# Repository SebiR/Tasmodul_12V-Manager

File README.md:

# 12V Power Management
A Tasmota compatible power selector for Caravans including automatic power source switching between on-board battery, car power and a mains PSU.
A INA226 measures the output voltage and current, the presence of the power sources are also available on GPIOs.

## Features
* Up to 15A (10A nom.)
* Fused inputs
* Current and voltage measurement
* Automatic source switching with priorities (hard-wired)

## Tasmota Configuration
Tasmota won't probe the INA226 unless full-scale current and the value of the shunt resistor are set.
 
`Sensor54 10 Return channel 1 shunt resistance and full scale current`

`Sensor54 11 [shunt_resistance] Set INA226 channel 1 shunt resistance in ohms, floating point`

`Sensor54 12 [full_scale_current] Set INA226 channel 1 full scale current in amperes, floating point`

So with the `Sensor54` command, we can set the current and the resistance for our board:

`Sensor54 11 0.002`

`Sensor54 12 15`

After that, we can see the current and the voltage in Tasmota.

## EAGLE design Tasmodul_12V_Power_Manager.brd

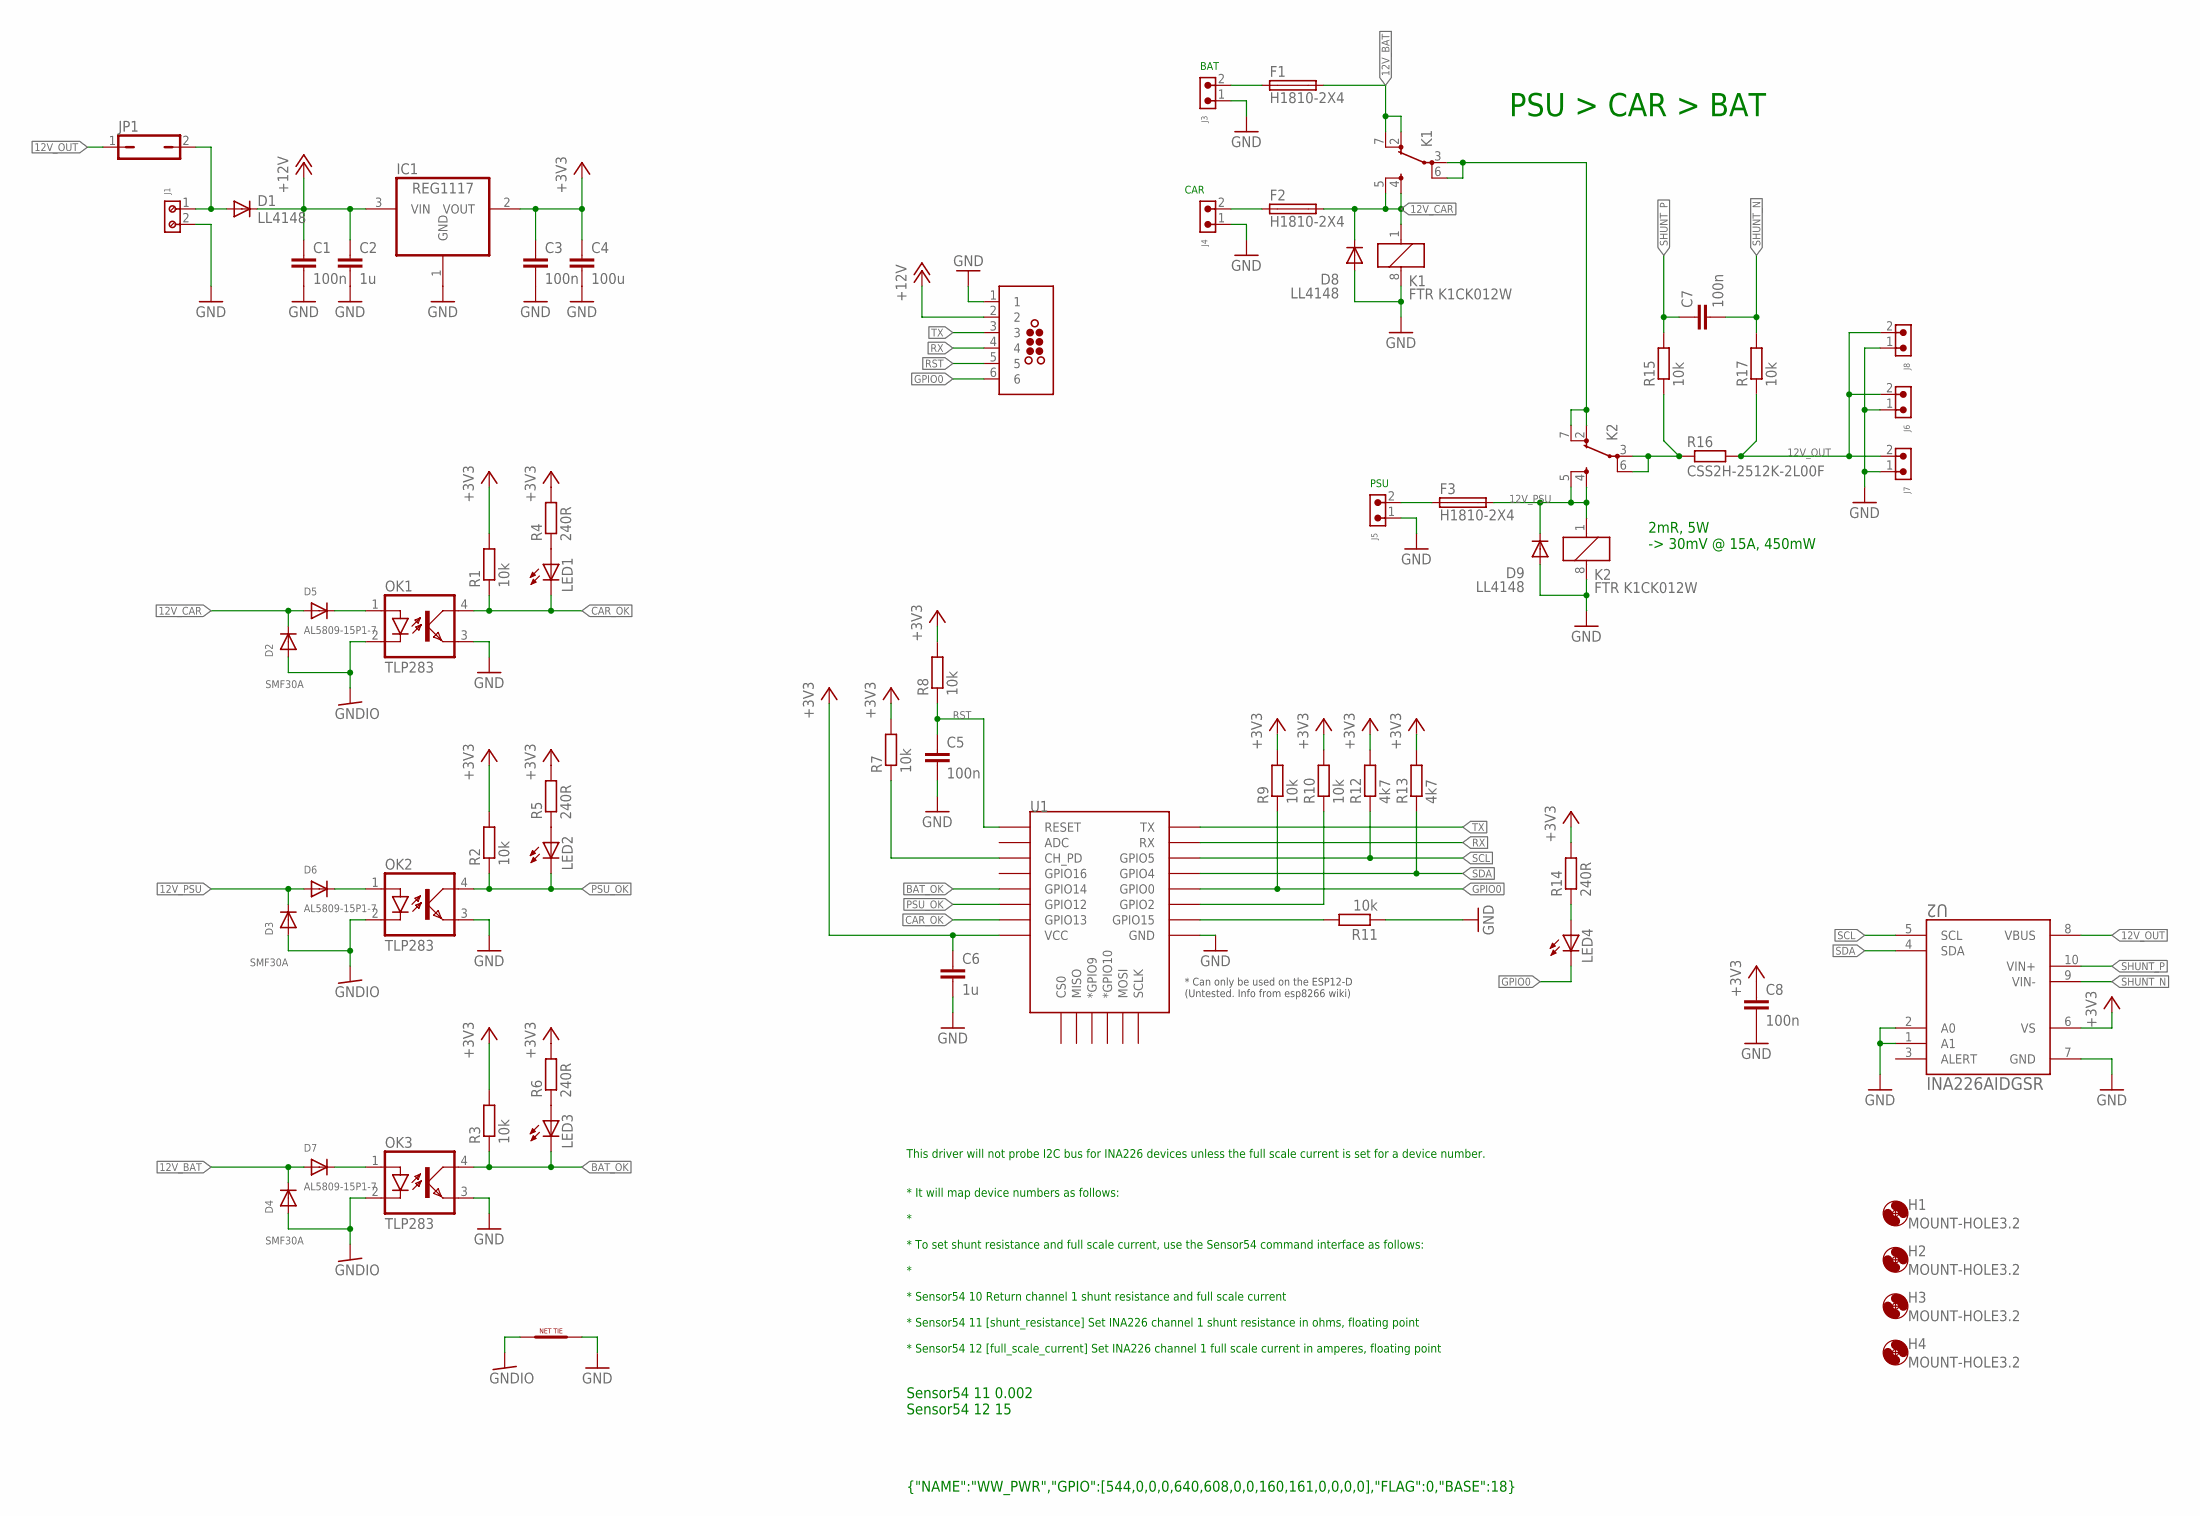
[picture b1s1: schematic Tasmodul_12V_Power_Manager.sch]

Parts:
C1, C3, C5, C7, C8: 100n; C0603
C2, C6: 1u; C0603
C4: 100u; C0603
D1, D8, D9: LL4148; MINIMELF
D2, D3, D4: SMF30A; SOD-123FL
D5, D6, D7: AL5809-15P1-7; SOD-123FL
F1, F2, F3: H1810-2X4
H1, H2, H3, H4: MOUNT-HOLE3.2; 3,2
IC1: REG1117; SOT223
J1: 691210910002
J2: TC2030-MCP-NL
J3, J4, J5, J6, J7, J8: 691313510002
JP1: JP1Q; JP1
K1, K2: FTR K1CK012W; FTR-K1C
LED1, LED2, LED3, LED4: LEDCHIP-LED0603; CHIP-LED0603
NT1: NET_TIE0.5MM; NET_TIE_0.5
OK1, OK2, OK3: TLP283; MINI-FLAT-4
R1, R2, R3, R7, R8, R9, R10, R11, R15, R17: 10k; R0603
R4, R5, R6, R14: 240R; R0603
R12, R13: 4k7; R0603
R16: CSS2H-2512K-2L00F
U1: ESP12ESMD; ESP12E-SMD
U2: INA226AIDGSR; DGS10

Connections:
12V_BAT: D4.C, D7.A, F1.B1 (2), F1.B2 (2), F1.B3 (2), F1.B4 (2), K1.2 (OA), K1.7 (OB)
12V_CAR: D2.C, D5.A, D8.C, F2.B1 (2), F2.B2 (2), F2.B3 (2), F2.B4 (2), K1.1, K1.4 (SA), K1.5 (SB)
12V_OUT: J6.2, J7.2, J8.2, JP1.1, R16.2, R17.1, U2.8 (VBUS)
12V_PSU: D3.C, D6.A, D9.C, F3.B1 (2), F3.B2 (2), F3.B3 (2), F3.B4 (2), K2.1, K2.4 (SA), K2.5 (SB)
+3V3: C3.1, C4.1, C6.1, C8.1, IC1.2 (VOUT), R1.2, R2.2, R3.2, R4.2, R5.2, R6.2, R7.2, R8.2, R9.2, R10.2, R12.2, R13.2, R14.2, U1.VCC, U2.6 (VS)
+12V: C1.1, C2.1, D1.C, IC1.3 (VIN), J2.2
BAT_OK: LED3.C, OK3.4 (COL), R3.1, U1.GPIO14
CAR_OK: LED1.C, OK1.4 (COL), R1.1, U1.GPIO13
GND: C1.2, C2.2, C3.2, C4.2, C5.2, C6.2, C8.2, D8.A, D9.A, IC1.1 (GND), J1.2, J2.1, J3.1, J4.1, J5.1, J6.1, J7.1, J8.1, K1.8 (2), K2.8 (2), NT1.NET2, OK1.3 (EMIT), OK2.3 (EMIT), OK3.3 (EMIT), R11.1, U1.GND, U2.1 (A1), U2.2 (A0), U2.7 (GND)
GNDIO: D2.A, D3.A, D4.A, NT1.NET1, OK1.2 (C), OK2.2 (C), OK3.2 (C)
GPIO0: J2.6, LED4.C, R9.1, U1.GPIO0
unnamed: LED1.A, R4.1
unnamed: F1.A1 (1), F1.A2 (1), F1.A3 (1), F1.A4 (1), J3.2
unnamed: D1.A, J1.1, JP1.2
unnamed: LED2.A, R5.1
unnamed: F3.A1 (1), F3.A2 (1), F3.A3 (1), F3.A4 (1), J5.2
unnamed: R7.1, U1.CH_PD
unnamed: R11.2, U1.GPIO15
unnamed: R10.1, U1.GPIO2
unnamed: LED4.A, R14.1
unnamed: LED3.A, R6.1
unnamed: K2.3 (PA), K2.6 (PB), R15.1, R16.1
unnamed: D5.C, OK1.1 (A)
unnamed: K1.3 (PA), K1.6 (PB), K2.2 (OA), K2.7 (OB)
unnamed: F2.A1 (1), F2.A2 (1), F2.A3 (1), F2.A4 (1), J4.2
unnamed: D6.C, OK2.1 (A)
unnamed: D7.C, OK3.1 (A)
PSU_OK: LED2.C, OK2.4 (COL), R2.1, U1.GPIO12
RST: C5.1, J2.5, R8.1, U1.RESET
RX: J2.4, U1.RXD0 (RX)
SCL: R12.1, U1.GPIO5, U2.5 (SCL)
SDA: R13.1, U1.GPIO4, U2.4 (SDA)
SHUNT_N: C7.2, R17.2, U2.9 (VIN-)
SHUNT_P: C7.1, R15.2, U2.10 (VIN+)
TX: J2.3, U1.TXD0 (TX)

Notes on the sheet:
BAT
PSU
This driver will not probe I2C bus for INA226 devices unless the full scale current is set for a device number. * It will map device numbers as follows: * * To set shunt resistance and full scale current, use the Sensor54 command interface as follows: * * Sensor54 10 Return channel 1 shunt resistan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
{"NAME":"WW_PWR","GPIO":[544,0,0,0,640,608,0,0,160,161,0,0,0,0],"FLAG":0,"BASE":18}
Sensor54 11 0.002 Sensor54 12 15
PSU > CAR > BAT
CAR
2mR, 5W -> 30mV @ 15A, 450mW

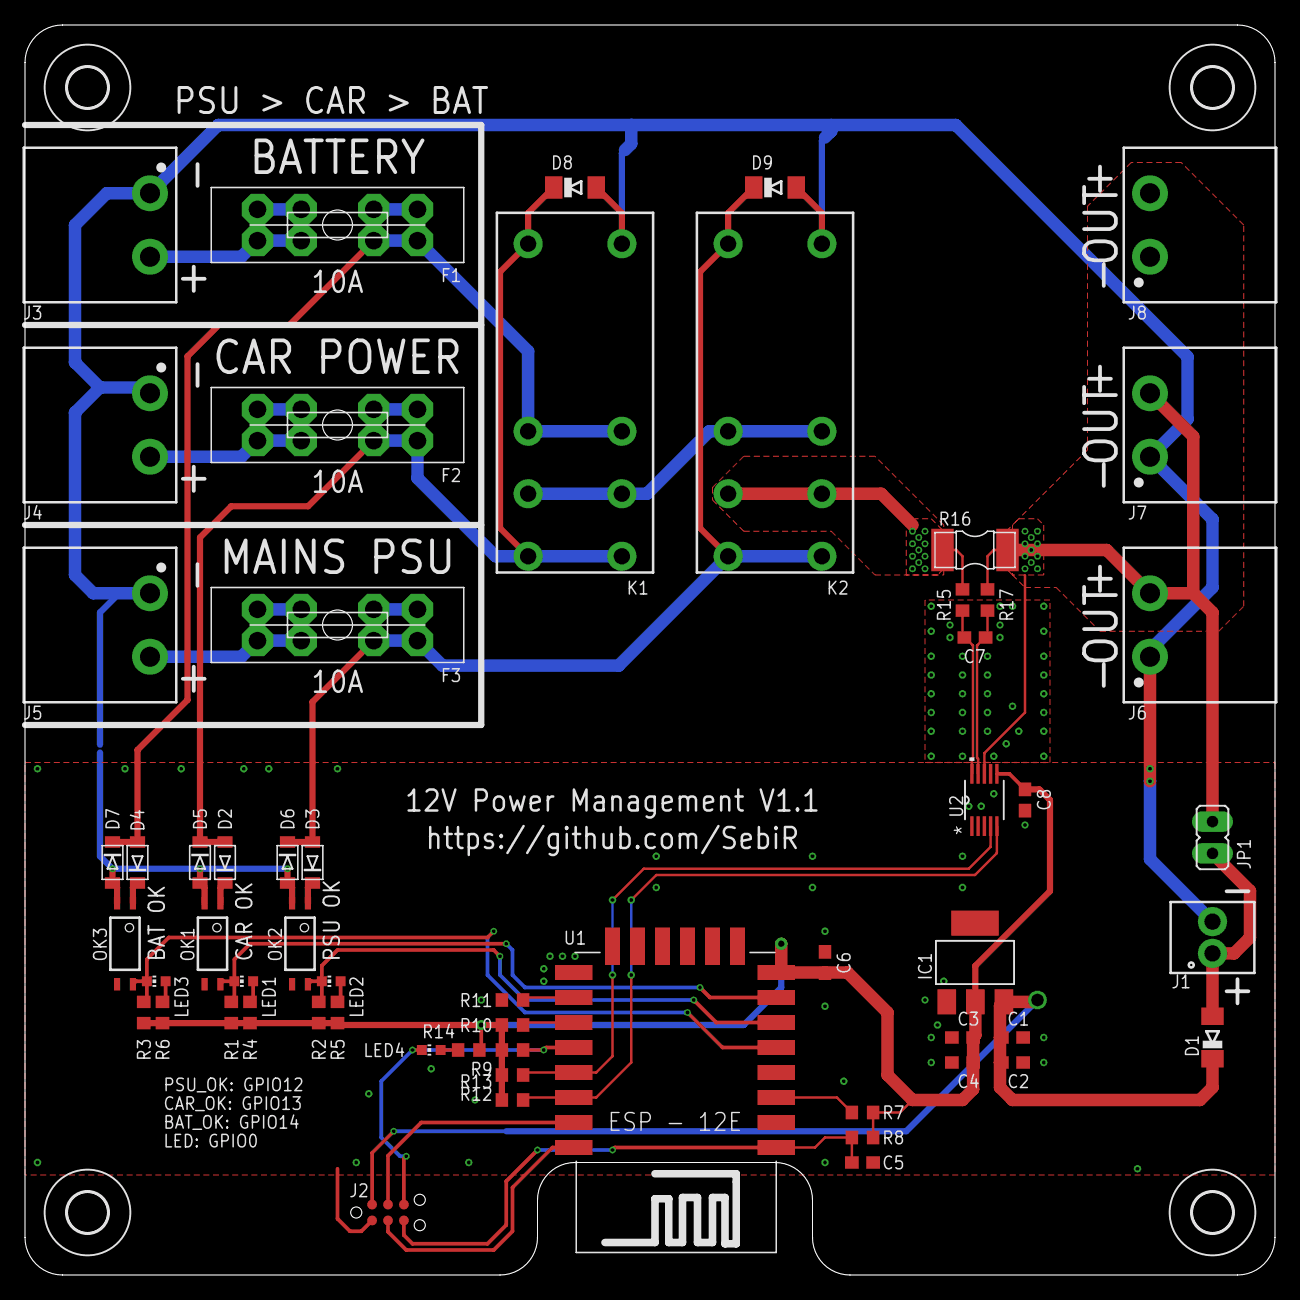
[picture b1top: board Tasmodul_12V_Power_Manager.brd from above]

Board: 2 copper layers, 100.0 x 100.0 mm, 63 parts (1 on the bottom side), 35 nets.

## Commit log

2023-08-05 removed unwanted files from other project (damn you c&p!)

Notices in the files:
parts and their libraries:
Wurth_Connectors_WR-TBL Pluggable Connec: Copyright: Würth Elektronik
tag-connect: ©2009 ROFA.cz - modified and updated by Robert Darlington ‹rdarlington@gmail.com›
COPYRIGHT: Copyright (C) 2022 Ultra Librarian. All rights reserved.
